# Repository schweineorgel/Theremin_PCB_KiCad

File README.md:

# Theremin_PCB_KiCad
Diseño en esquematico y PCB de un Theremin

Este proyecto se inició como aprendizaje y comparación entre Proteus 8 y KiCad 9.

## Comparación entre Proteus 8 y KiCad 9

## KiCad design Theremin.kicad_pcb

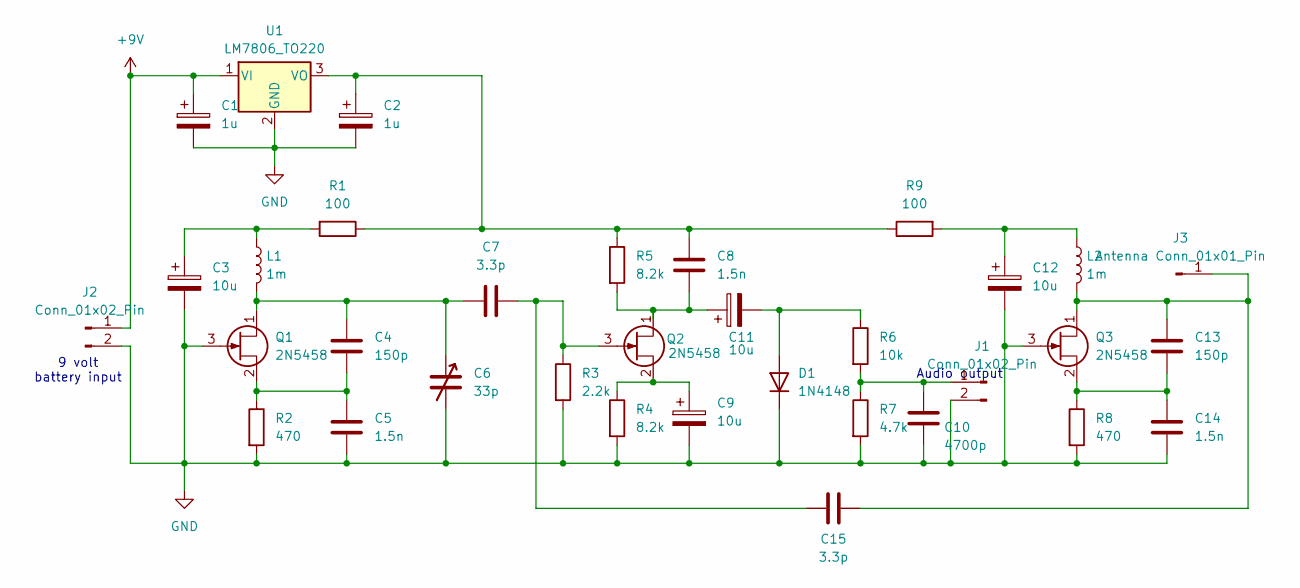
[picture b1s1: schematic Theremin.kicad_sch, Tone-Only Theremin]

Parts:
C1, C2: 1u; CP_Radial_D4.0mm_P1.50mm
C3, C9, C11, C12: 10u; CP_Radial_D4.0mm_P1.50mm
C4, C13: 150p; C_Disc_D3.0mm_W1.6mm_P2.50mm
C5, C8, C14: 1.5n; C_Disc_D3.0mm_W1.6mm_P2.50mm
C6: 33p; CP_Radial_D4.0mm_P1.50mm
C7, C15: 3.3p; C_Disc_D3.0mm_W1.6mm_P2.50mm
C10: 4700p; C_Rect_L4.6mm_W2.0mm_P2.50mm_MKS02_FKP02
D1: 1N4148; D_DO-35_SOD27_P7.62mm_Horizontal
J1, J2: Conn_01x02_Pin; SolderWire-0.1sqmm_1x02_P3.6mm_D0.4mm_OD1mm
J3: Antenna Conn_01x01_Pin; SolderWire-0.1sqmm_1x01_D0.4mm_OD1mm
L1, L2: 1m; L_Axial_L5.3mm_D2.2mm_P10.16mm_Horizontal_Vishay_IM-1
Q1, Q2, Q3: 2N5458; TO-92_Inline
R1, R9: 100; R_Axial_DIN0204_L3.6mm_D1.6mm_P7.62mm_Horizontal
R2, R8: 470; R_Axial_DIN0204_L3.6mm_D1.6mm_P7.62mm_Horizontal
R3: 2.2k; R_Axial_DIN0204_L3.6mm_D1.6mm_P7.62mm_Horizontal
R4, R5: 8.2k; R_Axial_DIN0204_L3.6mm_D1.6mm_P7.62mm_Horizontal
R6: 10k; R_Axial_DIN0204_L3.6mm_D1.6mm_P7.62mm_Horizontal
R7: 4.7k; R_Axial_DIN0204_L3.6mm_D1.6mm_P7.62mm_Horizontal
U1: LM7806_TO220; TO-220-3_Vertical

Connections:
+9V: C1.1, J2.1, U1.1 (VI)
GND: C1.2, C2.2, C3.2, C5.2, C6.2, C9.2, C10.2, C12.2, C14.2, D1.1 (K), J1.2, J2.2, Q1.3 (G), Q3.3 (G), R2.2, R3.2, R4.2, R7.2, R8.2, U1.2 (GND)
unnamed: C3.1, L1.1, R1.2
unnamed: C12.1, L2.1, R9.2
unnamed: C11.2, D1.2 (A), R6.1
unnamed: C10.1, J1.1, R6.2, R7.1
unnamed 6: C13.1, C15.2, J3.1, L2.2, Q3.1 (D); also elsewhere on the board
unnamed: C4.1, C6.1, C7.1, L1.2, Q1.1 (D)
unnamed: C4.2, C5.1, Q1.2 (S), R2.1
unnamed: C8.2, C11.1, Q2.1 (D), R5.2
unnamed: C7.2, C15.1, Q2.3 (G), R3.1
unnamed: C9.1, Q2.2 (S), R4.1
unnamed: C13.2, C14.1, Q3.2 (S), R8.1
unnamed: C2.1, C8.1, R1.1, R5.1, R9.1, U1.3 (VO)

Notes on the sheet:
Audio output
9 volt battery input

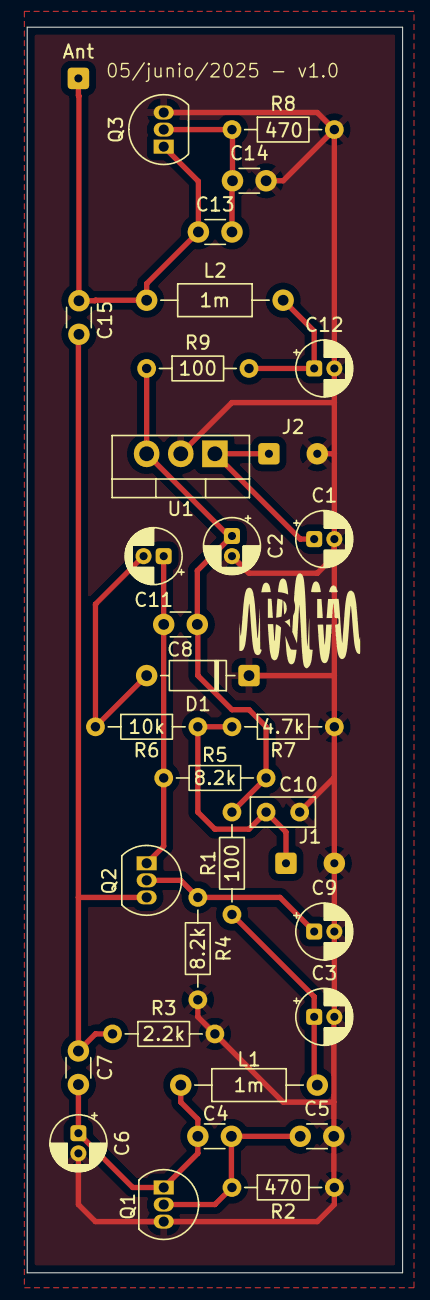
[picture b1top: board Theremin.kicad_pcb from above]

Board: 2 copper layers, 27.9 x 92.7 mm, 34 parts (0 on the bottom side), 14 nets.

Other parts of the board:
Ant: Antena; SolderWire-0.1sqmm_1x01_D0.4mm_OD1mm

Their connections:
unnamed 6: Ant.1; also elsewhere on the board

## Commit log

2025-06-05 Agregar archivos de proyecto KiCad
2025-06-05 Agregar archivos de proyecto con .gitignore incluid
2025-06-05 PCB y esquemático posiblemente finalizado
